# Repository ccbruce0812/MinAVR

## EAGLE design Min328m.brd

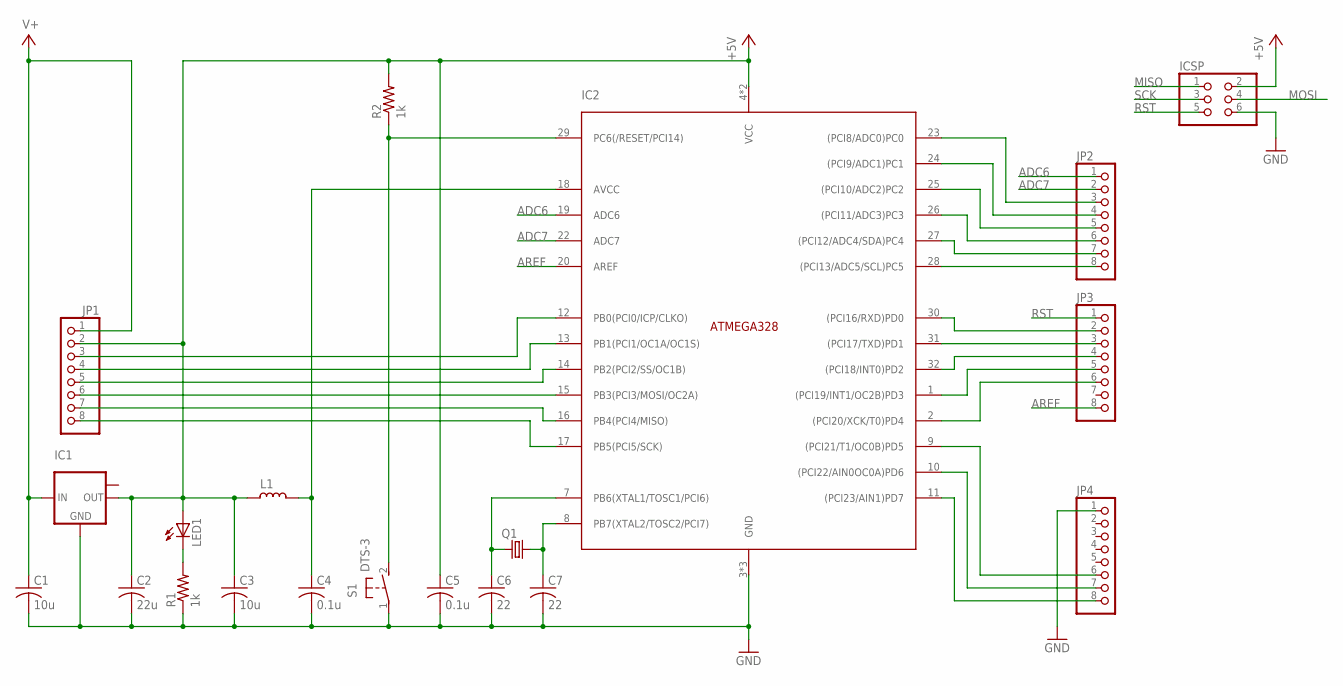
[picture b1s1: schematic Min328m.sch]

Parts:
C1: 10u; C1210K
C2: 22u; C1210K
C3: 10u; C0805K
C4, C5: 0.1u; C0805K
C6, C7: 22; C0805K
IC1: LM1117MPX-5.0; SOT223
IC2: ATMEGA328P; TQFP32-08
ICSP: PINHD-2X3; 2X03
JP1, JP2, JP3, JP4: PINHD-1X8; 1X08
L1: L_0805; L0805
LED1: LEDCHIPLED_0805; CHIPLED_0805
Q1: CRYSTALSM49; SM49
R1, R2: 1k; R0805
S1: DTS-3

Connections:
+5V: C2.1, C3.1, C5.1, IC1.2 (OUT), IC2.4 (VCC), IC2.6 (VCC), ICSP.2, JP1.2, L1.2, LED1.A, R2.2
ADC6: IC2.19 (ADC6), JP2.1
ADC7: IC2.22 (ADC7), JP2.2
AREF: IC2.20 (AREF), JP3.8
GND: C1.2, C2.2, C3.2, C4.2, C5.2, C6.2, C7.2, IC1.1 (GND), IC2.3 (GND), IC2.5 (GND), IC2.21 (GND), ICSP.6, JP4.1, R1.1, S1.1
MISO: IC2.16 (PB4(PCI4/MISO)), ICSP.1, JP1.7
MOSI: IC2.15 (PB3(PCI3/MOSI/OC2A)), ICSP.4, JP1.6
unnamed: LED1.C, R1.2
unnamed: IC2.11 ((PCI23/AIN1)PD7), JP4.8
unnamed: IC2.28 ((PCI13/ADC5/SCL)PC5), JP2.8
unnamed: C4.1, IC2.18 (AVCC), L1.1
unnamed: IC2.10 ((PCI22/AIN0OC0A)PD6), JP4.7
unnamed: IC2.27 ((PCI12/ADC4/SDA)PC4), JP2.7
unnamed: IC2.30 ((PCI16/RXD)PD0), JP3.2
unnamed: IC2.31 ((PCI17/TXD)PD1), JP3.3
unnamed: IC2.32 ((PCI18/INT0)PD2), JP3.4
unnamed: IC2.9 ((PCI21/T1/OC0B)PD5), JP4.6
unnamed: IC2.26 ((PCI11/ADC3)PC3), JP2.6
unnamed: IC2.25 ((PCI10/ADC2)PC2), JP2.5
unnamed: IC2.24 ((PCI9/ADC1)PC1), JP2.4
unnamed: IC2.23 ((PCI8/ADC0)PC0), JP2.3
unnamed: IC2.14 (PB2(PCI2/SS/OC1B)), JP1.5
unnamed: IC2.13 (PB1(PCI1/OC1A/OC1S)), JP1.4
unnamed: IC2.12 (PB0(PCI0/ICP/CLKO)), JP1.3
unnamed: IC2.1 ((PCI19/INT1/OC2B)PD3), JP3.5
unnamed: IC2.2 ((PCI20/XCK/T0)PD4), JP3.6
RST: IC2.29 (PC6(/RESET/PCI14)), ICSP.5, JP3.1, R2.1, S1.2
SCK: IC2.17 (PB5(PCI5/SCK)), ICSP.3, JP1.8
V+: C1.1, IC1.3 (IN), JP1.1
XTAL1: C6.1, IC2.7 (PB6(XTAL1/TOSC1/PCI6)), Q1.2
XTAL2: C7.1, IC2.8 (PB7(XTAL2/TOSC2/PCI7)), Q1.1

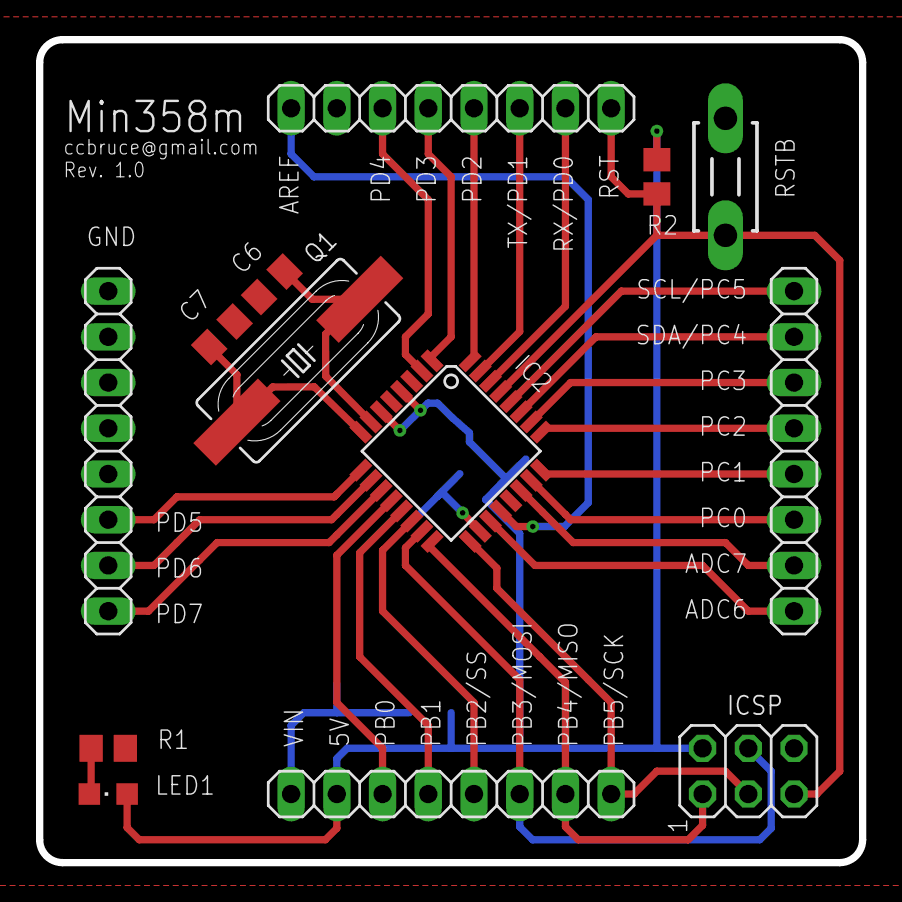
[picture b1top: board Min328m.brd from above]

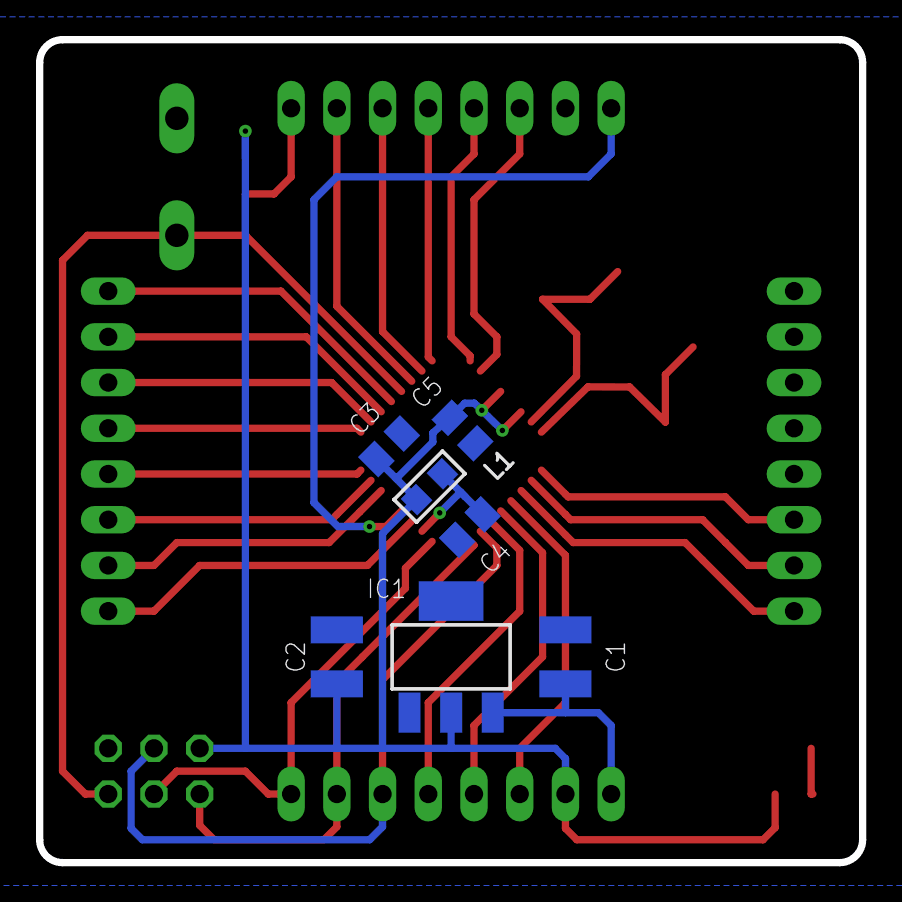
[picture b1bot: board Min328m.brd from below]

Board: 2 copper layers, 45.7 x 45.7 mm, 20 parts (7 on the bottom side), 31 nets.

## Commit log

2018-06-24 Draft version.

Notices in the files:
parts and their libraries:
rc-master-smd: Copyright (C) 2007-2008, Bob Starr
